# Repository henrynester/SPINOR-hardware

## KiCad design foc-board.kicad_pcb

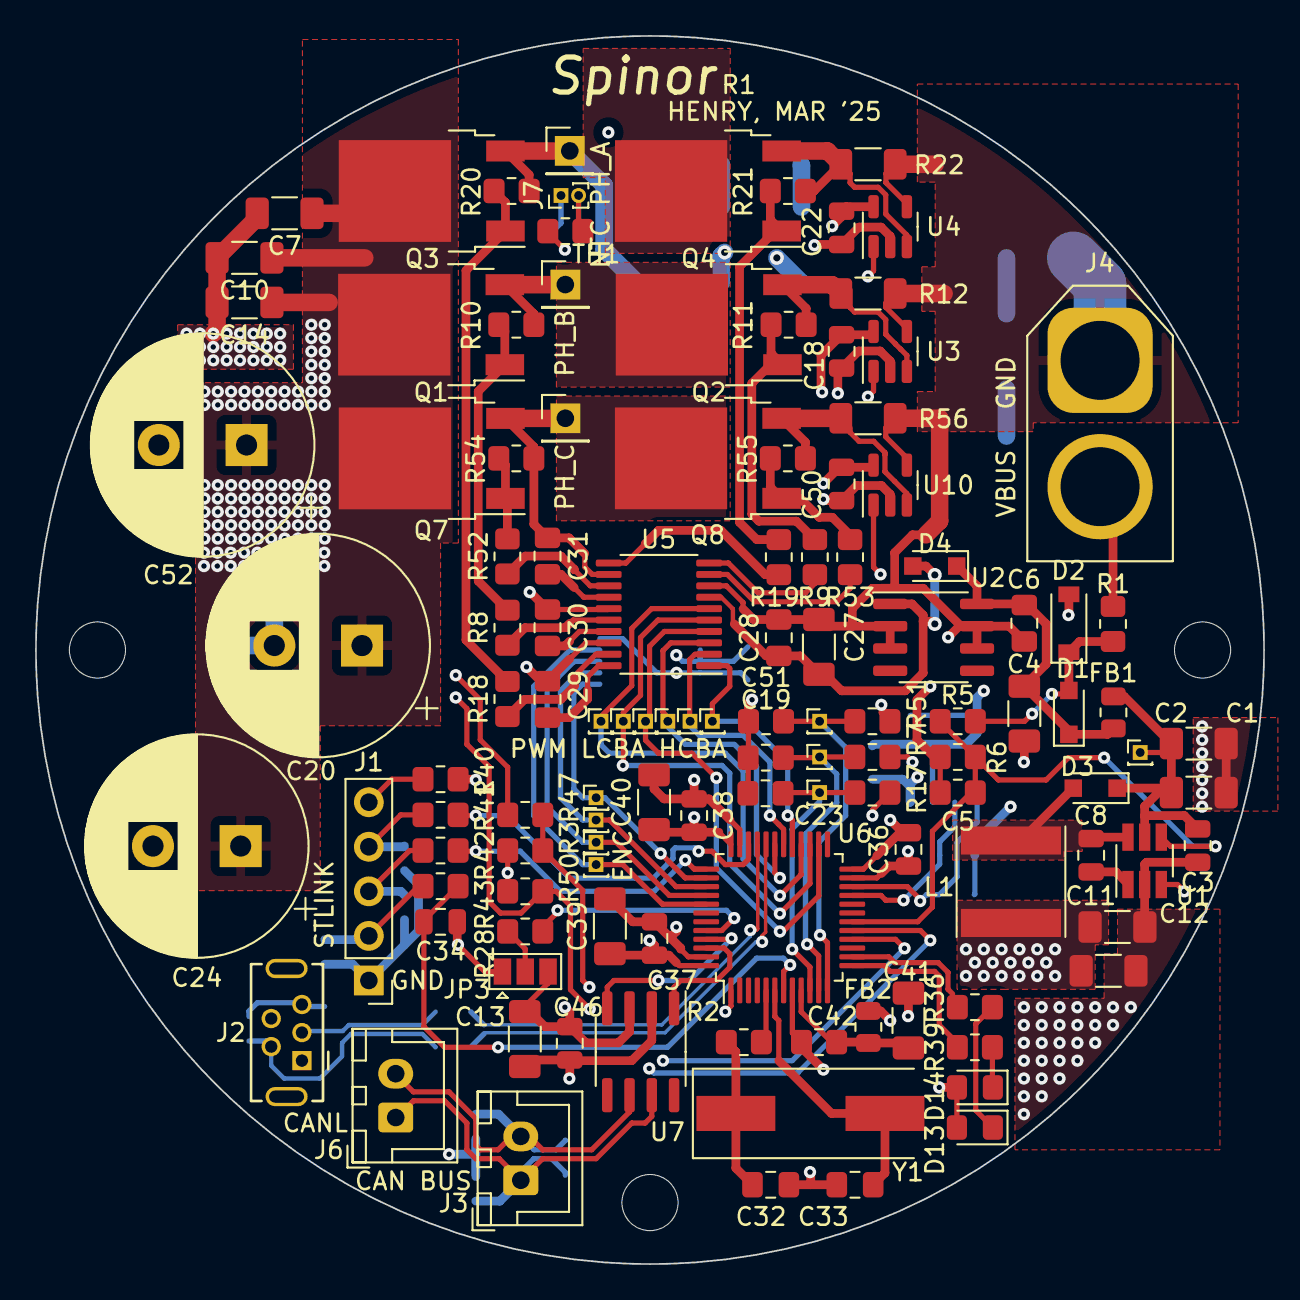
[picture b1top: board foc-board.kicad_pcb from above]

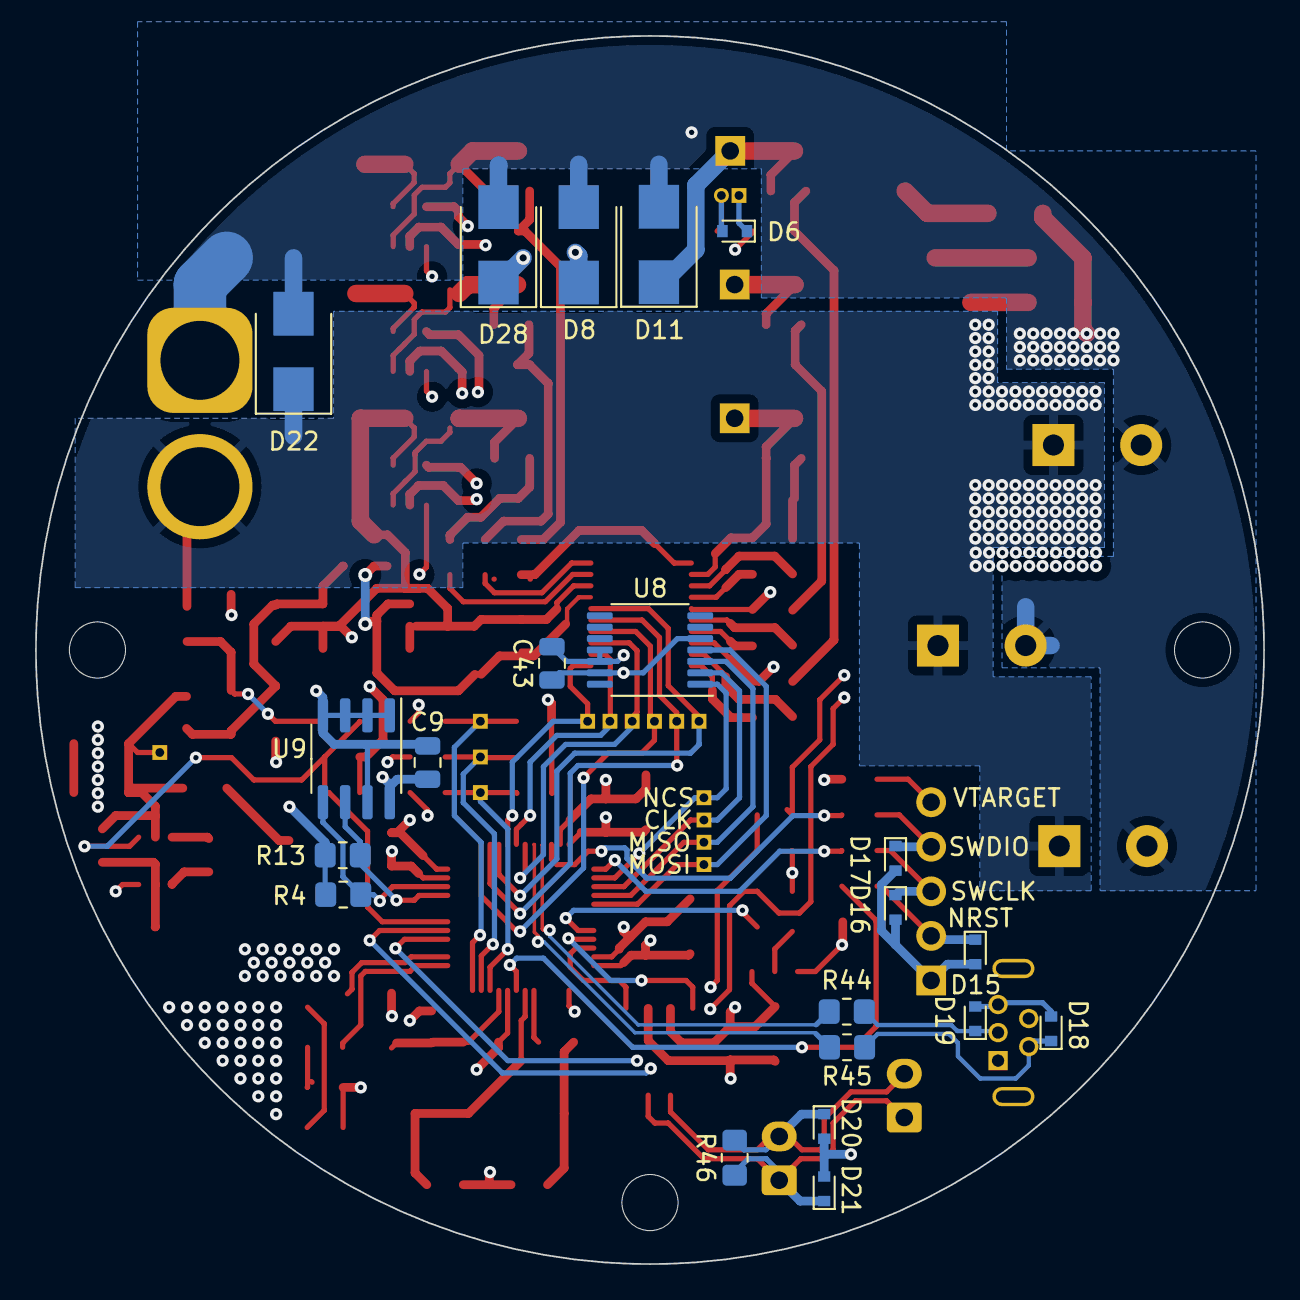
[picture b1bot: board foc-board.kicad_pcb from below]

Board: 4 copper layers, 70.0 x 70.0 mm, 143 parts (21 on the bottom side), 77 nets.

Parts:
C1, C2, C4, C7, C10, C13, C14, C27, C39, C40, C41: 4.7u 50V; C_1206_3216Metric_Pad1.33x1.80mm_HandSolder
C3, C8, C9, C18, C22, C34, C36, C37, C38, C43, C46, C50: 100n 50V; C_0805_2012Metric
C5, C19, C23, C42, C51: 10n; R_0805_2012Metric_Pad1.20x1.40mm_HandSolder
C6, C29, C30, C31: 470n 50V; C_0805_2012Metric_Pad1.18x1.45mm_HandSolder
C11, C12: 10u 25V; C_1206_3216Metric_Pad1.33x1.80mm_HandSolder
C20, C24, C52: 470u 50V; CP_Radial_D12.5mm_P5.00mm
C28: 100n 50V; C_0805_2012Metric_Pad1.18x1.45mm_HandSolder
C32, C33: 27pF; C_0805_2012Metric_Pad1.18x1.45mm_HandSolder
D1, D3, D4: 40V 1A; D_SOD-323_HandSoldering
D2: 26V Z; D_SOD-123
D6, D15, D16, D17, D18, D19, D20, D21: 3.3V TVS; D_SOD-523
D8, D11, D22, D28: 26V TVS; D_SMB
D13: RED; LED_0805_2012Metric_Pad1.15x1.40mm_HandSolder
D14: BLU; LED_0805_2012Metric_Pad1.15x1.40mm_HandSolder
FB1, FB2: 120R@100MHz; R_0805_2012Metric
H2, H3, H4: MountingHole; MountingHole_3.2mm_M3
J1: PinHeader_1x05_P2.54mm_Vertical
J2: USB_B_Mini; USB_Mini-B_Tensility_54-00023_Vertical
J3, J6: Conn_01x02_Male; JST_XH_B2B-XH-A_1x02_P2.50mm_Vertical
J4: Conn_01x02_Male; AMASS_XT60-M_1x02_P7.20mm_Vertical
J5, J8, J9: Conn_01x01; PinHeader_1x01_P2.54mm_Vertical
J7: Conn_01x02; PinHeader_1x02_P1.00mm_Vertical
JP3: SolderJumper-3_P1.3mm_Open_Pad1.0x1.5mm
L1: 33u; L_Taiyo-Yuden_NR-60xx
Q1, Q2, Q3, Q4, Q7, Q8: TK90S06N1L; TO-252-2
R1, R8, R9, R18, R19, R52, R53: 15R 1/4W; R_0805_2012Metric_Pad1.20x1.40mm_HandSolder
R2: 720R; R_0805_2012Metric_Pad1.20x1.40mm_HandSolder
R3, R4, R13, R50: 4.7k; R_0805_2012Metric_Pad1.20x1.40mm_HandSolder
R5, R28: 100k; R_0805_2012Metric_Pad1.20x1.40mm_HandSolder
R6, R10, R11, R20, R21, R54, R55: 10k; R_0805_2012Metric_Pad1.20x1.40mm_HandSolder
R7, R17, R39, R40, R41, R42, R43, R44, R45, R47, R51: 100R; R_0805_2012Metric_Pad1.20x1.40mm_HandSolder
R12, R22, R56: 1m 1.5W; R_1206_3216Metric_Pad1.30x1.75mm_HandSolder
R36: 330R; R_0805_2012Metric_Pad1.20x1.40mm_HandSolder
R46: 120R 1/4W; R_0805_2012Metric_Pad1.20x1.40mm_HandSolder
TH1: 10k NTC; R_0805_2012Metric_Pad1.20x1.40mm_HandSolder
TP1, TP4, TP5, TP6, TP7, TP8, TP9, TP10, TP11, TP12, TP13, TP14, TP15, TP27: PinHeader_1x01_P1.00mm_Vertical
U1: TPS560430X3FDBVR; SOT-23-6_Handsoldering
U2: L78L12ABD-TR; SOIC-8_3.9x4.9mm_P1.27mm
U3, U4, U10: INA180A3; SOT-23-5
U5: DRV8300DPWR; TSSOP-20_4.4x6.5mm_P0.65mm
U6: STM32F072CBT6; LQFP-48_7x7mm_P0.5mm
U7: SN65HVD232; SOIC-8_3.9x4.9mm_P1.27mm
U8: AS5047D; TSSOP-14_4.4x5mm_P0.65mm
U9: 24LC08; SOIC-8_3.9x4.9mm_P1.27mm
Y1: 8MHz 18pF; Crystal_SMD_HC49-SD

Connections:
+15V: C27.1, C28.1, D4.2 (A), U2.1 (OUT), U5.7 (GVDD)
/gate_driver/BOOST_A: C29.1, U5.20 (BSTA)
/gate_driver/BOOST_B: C30.1, U5.17 (BSTB)
/gate_driver/BOOST_C: C31.1, U5.14 (BSTC)
/gate_driver/GATE_H_A: R18.1, U5.19 (GHA)
/gate_driver/GATE_H_B: R8.1, U5.16 (GHB)
/gate_driver/GATE_H_C: R52.1, U5.13 (GHC)
/gate_driver/GATE_L_A: R19.1, U5.11 (GLA)
/gate_driver/GATE_L_B: R9.1, U5.10 (GLB)
/gate_driver/GATE_L_C: R53.1, U5.9 (GLC)
/gate_driver/PWMH_A: TP13.1, U5.1 (INHA), U6.29 (PA8)
/gate_driver/PWMH_B: TP14.1, U5.2 (INHB), U6.30 (PA9)
/gate_driver/PWMH_C: TP15.1, U5.3 (INHC), U6.31 (PA10)
/gate_driver/PWML_A: TP4.1, U5.4 (INLA), U6.26 (PB13)
/gate_driver/PWML_B: TP8.1, U5.5 (INLB), U6.27 (PB14)
/gate_driver/PWML_C: TP9.1, U5.6 (INLC), U6.28 (PB15)
/microcontroller/BOOT0: R28.2, U6.44 (BOOT0)
/microcontroller/CANH: D20.1 (K), J3.2, J6.2, R46.2, U7.6 (CANL)
/microcontroller/CANL: D21.1 (K), J3.1, J6.1, R46.1, U7.7 (CANH)
/microcontroller/CAN_RX: U6.45 (PB8), U7.4 (R)
/microcontroller/CAN_TX: U6.46 (PB9), U7.1 (D)
/microcontroller/ENC_CLK: TP7.1, U6.39 (PB3), U8.2 (CLK)
/microcontroller/ENC_MISO: TP10.1, U6.40 (PB4), U8.3 (MISO)
/microcontroller/ENC_MOSI: TP11.1, U6.41 (PB5), U8.4 (MOSI)
/microcontroller/ENC_NCS: TP12.1, U6.38 (PA15), U8.1 (~CS)
/microcontroller/NRST: C34.2, R43.2, U6.7 (NRST)
/microcontroller/NRST_RAW: D15.1 (K), J1.2, R43.1
/microcontroller/ROM_SCL: R13.2, U6.21 (PB10), U9.6 (SCL)
/microcontroller/ROM_SDA: R4.2, U6.22 (PB11), U9.5 (SDA)
/microcontroller/SWCLK: R42.2, U6.37 (PA14)
/microcontroller/SWCLK_RAW: D16.1 (K), J1.3, R42.1
/microcontroller/SWDIO: R41.2, U6.34 (PA13)
/microcontroller/SWDIO_RAW: D17.1 (K), J1.4, R41.1
/microcontroller/USB_D+: R44.2, U6.33 (PA12)
/microcontroller/USB_D-: R45.2, U6.32 (PA11)
/microcontroller/VTARGET: J1.5, R40.1
/power_stage_A/IL_SENSE: C23.1, R17.1, TP6.1, U6.10 (PA0)
/power_stage_A/ISENSE_P: Q4.3 (S), R21.2, R22.1, U4.3 (+)
/power_stage_B/IL_SENSE: C19.1, R7.1, TP5.1, U6.11 (PA1)
/power_stage_B/ISENSE_P: Q2.3 (S), R11.2, R12.1, U3.3 (+)
/power_stage_C/IL_SENSE: C51.1, R51.1, TP27.1, U6.12 (PA2)
/power_stage_C/ISENSE_P: Q8.3 (S), R55.2, R56.1, U10.3 (+)
/rails/TPS_SW: C8.2, D3.2 (A), L1.1, U1.6 (SW)
/rails/VBUS_PROT: D1.2 (A), D2.1 (K), R1.2, R5.1
/rails/VBUS_PROT_HELDUP: C4.1, C6.1, D1.1 (K), D4.1 (K), FB1.1, U2.8 (IN)
/rails/VBUS_PROT_HELDUP_FILT: C1.1, C2.1, C3.2, D3.1 (K), FB1.2, TP1.1, U1.5 (VIN)
/thermistors/NTC_MTR_RAW: D6.1 (K), J7.1, R47.2
GND: C1.2, C2.2, C3.1, C4.2, C5.2, C6.2, C7.2, C9.1, C10.2, C11.2, C12.2, C13.2, C14.2, C18.1, C19.2, C20.2, C22.1, C23.2, C24.2, C27.2, C28.2, C32.1, C33.1, C34.1, C36.1, C37.1, C38.1, C39.2, C40.2, C41.2, C42.2, C43.1, C46.1, C50.1, C51.2, C52.2, D2.2 (A), D6.2 (A), D8.2 (A), D11.2 (A), D15.2 (A), D16.2 (A), D17.2 (A), D18.2 (A), D19.2 (A), D20.2 (A), D21.2 (A), D22.2 (A), D28.2 (A), J1.1, J2.5 (GND), J4.1, J7.2, JP3.1 (A), R6.2, R12.2, R22.2, R56.2, TH1.2, U1.2 (GND), U2.2 (GND), U2.3 (GND), U2.6 (GND), U2.7 (GND), U3.2 (GND), U3.4 (-), U4.2 (GND), U4.4 (-), U5.8 (GND), U6.8 (VSSA), U6.23 (VSS), U6.35 (VSS), U6.47 (VSS), U7.2 (GND), U8.5 (TST), U8.13 (GND), U9.1 (A0), U9.2 (A1), U9.3 (A2), U9.4 (GND), U9.7 (WP), U10.2 (GND), U10.4 (-)
LED_A: R36.1, U6.14 (PA4)
LED_B: R39.1, U6.13 (PA3)
NTC_FET: R50.2, TH1.1, U6.17 (PA7)
NTC_MTR: R3.2, R47.1, U6.16 (PA6)
unnamed: C8.1, U1.1 (CB)
unnamed: C32.2, R2.2, Y1.1
unnamed: C33.2, U6.6 (PF1), Y1.2
unnamed: D13.1 (K), R36.2
unnamed: D14.1 (K), R39.2
unnamed: D18.1 (K), J2.2 (D-), R45.1
unnamed: D19.1 (K), J2.3 (D+), R44.1
unnamed: JP3.2 (C), R28.1
unnamed: Q1.1 (G), R8.2, R10.1
unnamed: Q2.1 (G), R9.2, R11.1
unnamed: Q3.1 (G), R18.2, R20.1
unnamed: Q4.1 (G), R19.2, R21.1
unnamed: Q7.1 (G), R52.2, R54.1
unnamed: Q8.1 (G), R53.2, R55.1
unnamed: R2.1, U6.5 (PF0)
unnamed: R7.2, U3.1
unnamed: R17.2, U4.1
unnamed: R51.2, U10.1
PHASE_A: C29.2, D11.1 (K), J5.1, Q3.3 (S), Q4.2 (D), R20.2, U5.18 (SHA)
PHASE_B: C30.2, D8.1 (K), J8.1, Q1.3 (S), Q2.2 (D), R10.2, U5.15 (SHB)
PHASE_C: C31.2, D28.1 (K), J9.1, Q7.3 (S), Q8.2 (D), R54.2, U5.12 (SHC)
VBUS: C7.1, C10.1, C14.1, C20.1, C24.1, C52.1, D22.1 (K), J4.2, Q1.2 (D), Q3.2 (D), Q7.2 (D), R1.1
VBUS_SENSE: C5.1, R5.2, R6.1, U1.4 (EN), U6.18 (PB0)
VDD: C9.2, C11.1, C12.1, C13.1, C18.2, C22.2, C36.2, C37.2, C38.2, C39.1, C40.1, C43.2, C46.2, C50.2, D13.2 (A), D14.2 (A), FB2.1, JP3.3 (B), L1.2, R3.1, R4.1, R13.1, R40.2, R50.1, U1.3 (FB), U3.5 (V+), U4.5 (V+), U6.1 (VBAT), U6.24 (VDD), U6.36 (VDDIO2), U6.48 (VDD), U7.3 (VCC), U8.11 (VDD), U8.12 (VDD3V3), U9.8 (VCC), U10.5 (V+)
VDDA: C41.1, C42.1, FB2.2, U6.9 (VDDA)

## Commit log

2025-03-19 1st cmt
2025-03-20 gerber generation
2025-03-20 add schem
